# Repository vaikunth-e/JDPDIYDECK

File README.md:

STM32 audio effect processor with custom PCB

[Demo](https://youtu.be/CMMS7bL4tLE)

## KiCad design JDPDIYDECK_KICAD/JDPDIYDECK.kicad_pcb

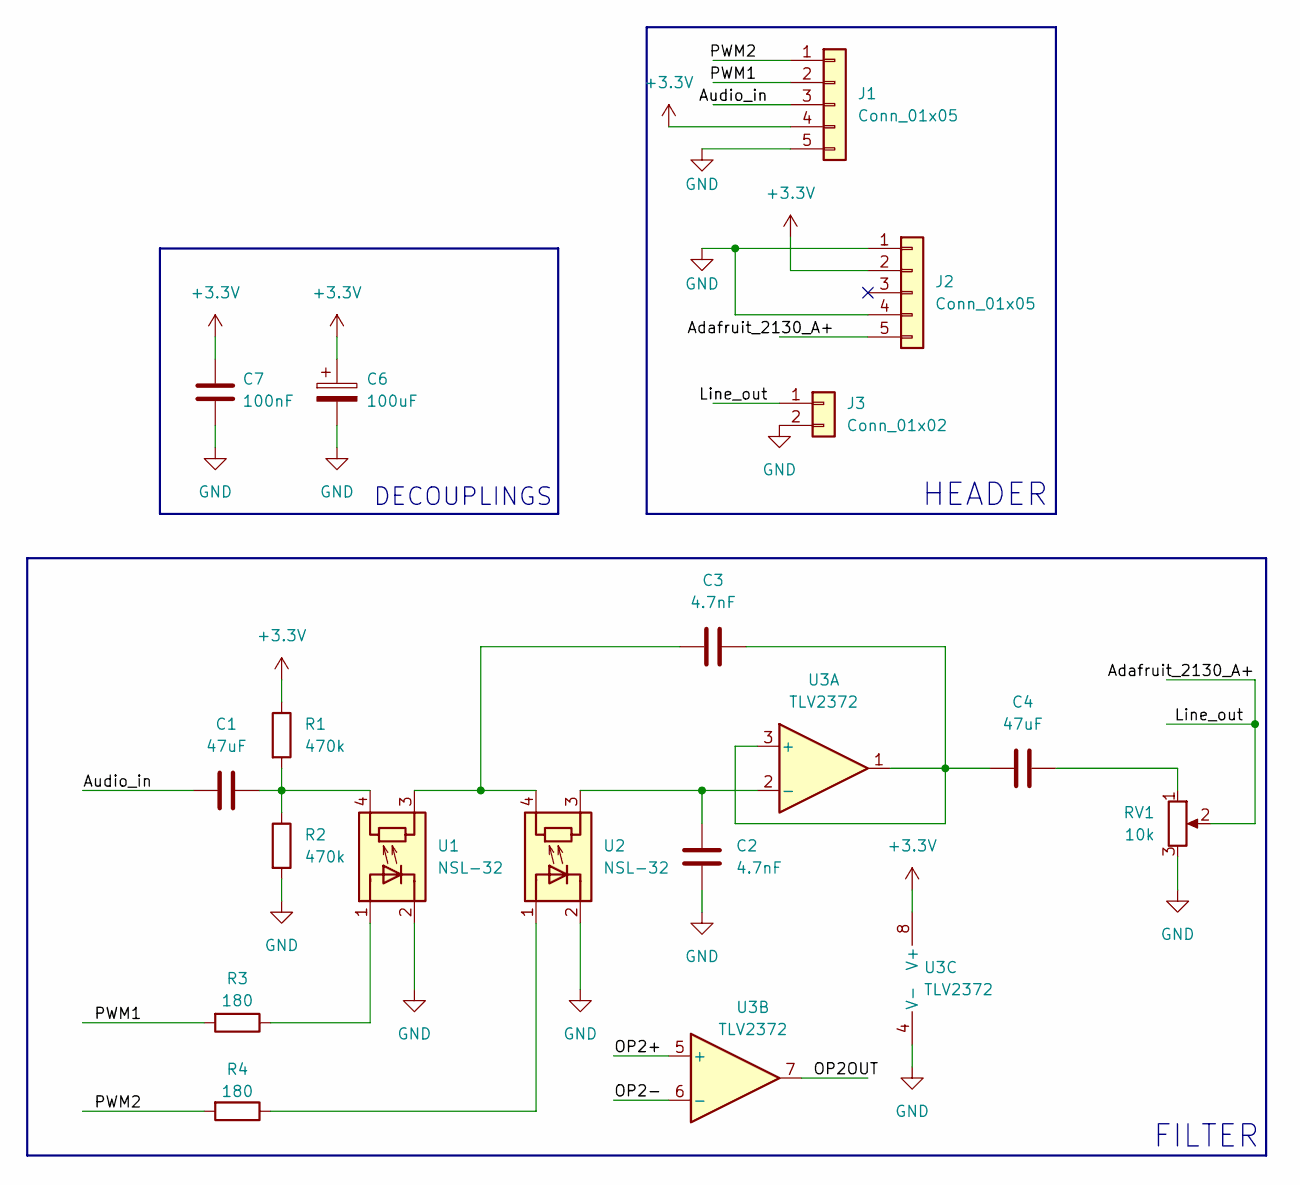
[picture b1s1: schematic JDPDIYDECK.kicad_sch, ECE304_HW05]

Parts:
C1, C4: 47uF; CAP_RDEC71E476MWK1H03B
C2, C3: 4.7nF; CAPRB500W50L400T250H550
C6: 100uF; CP_Radial_D5.0mm_P2.00mm
C7: 100nF; C_Rect_L4.0mm_W2.5mm_P2.50mm
J1: Conn_01x05; PinHeader_1x05_P2.54mm_Vertical
J2: Conn_01x05; PinSocket_1x05_P2.54mm_Vertical
J3: Conn_01x02; PinSocket_1x02_P2.54mm_Vertical
R1, R2: 470k; R_Axial_DIN0207_L6.3mm_D2.5mm_P10.16mm_Horizontal
R3, R4: 180; R_Axial_DIN0207_L6.3mm_D2.5mm_P10.16mm_Horizontal
RV1: 10k; Potentiometer_Bourns_PTV09A-1_Single_Vertical
U1, U2: NSL-32; Luna_NSL-32
U3: TLV2372; P8

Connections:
+3.3V: C6.1, C7.1, J1.4, J2.2, R1.1, U3.8 (V+)
/Adafruit_2130_A+: J2.5, J3.1, RV1.2
/Audio_in: C1.1, J1.3
/OP2+: U3.5 (+)
/OP2-: U3.6 (-)
/OP2OUT: U3.7
/PWM1: J1.2, R3.2
/PWM2: J1.1, R4.2
GND: C2.2, C6.2, C7.2, J1.5, J2.1, J2.4, J3.2, R2.2, RV1.3, U1.2 (K), U2.2 (K), U3.4 (V-)
unnamed: C1.2, R1.2, R2.1, U1.4 (R)
unnamed: C3.2, U1.3 (R), U2.4 (R)
unnamed: C4.2, RV1.1
unnamed: R3.1, U1.1 (A)
unnamed: R4.1, U2.1 (A)
unnamed: C3.1, C4.1, U3.1, U3.3 (+)
unnamed: C2.1, U2.3 (R), U3.2 (-)

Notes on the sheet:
HEADER
DECOUPLINGS
FILTER

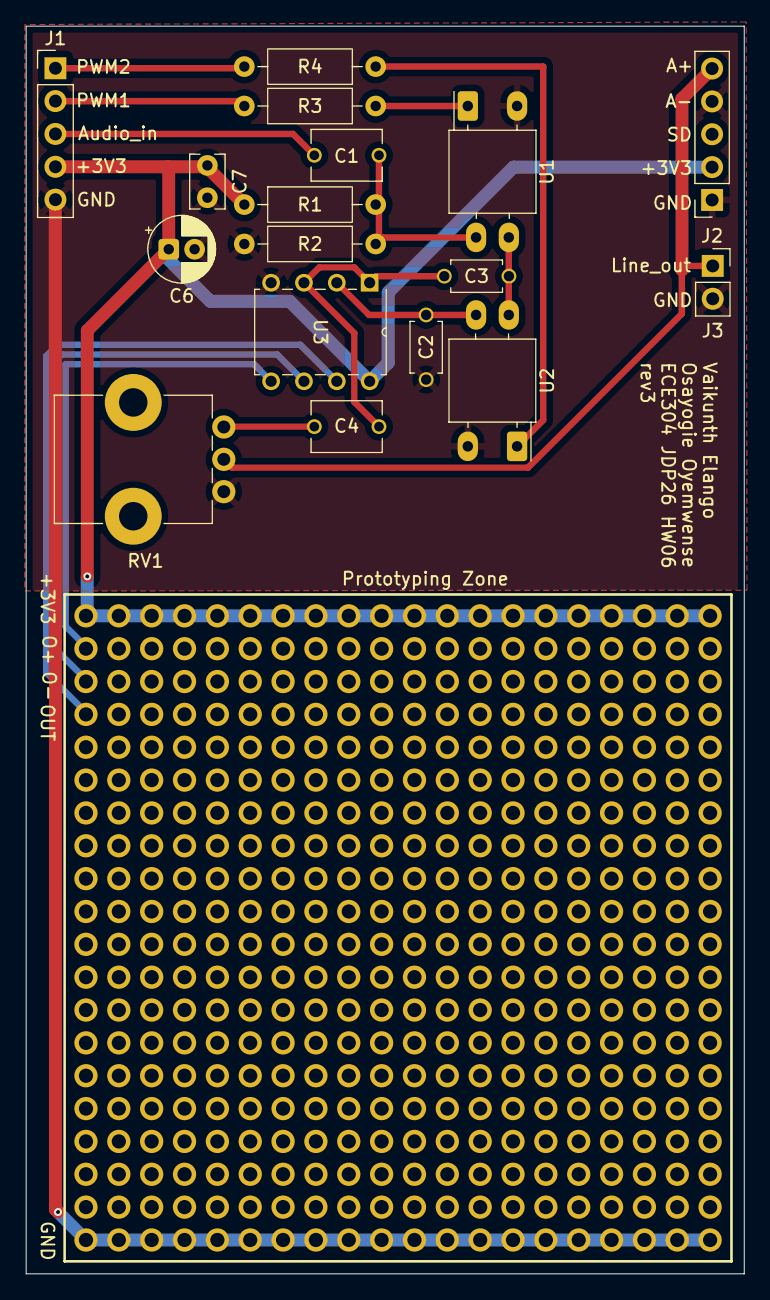
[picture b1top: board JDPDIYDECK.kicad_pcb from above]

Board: 2 copper layers, 55.5 x 96.5 mm, 17 parts (0 on the bottom side), 13 nets.

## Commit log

2026-04-25 circuit schematic
2026-04-26 KICAD files
2026-05-06 minor changes
2026-05-06 added button + 44.1 kHz
2026-05-08 ring modulation with triangle
2026-05-08 minor change
2026-05-12 Update project description in README
2026-05-12 Add demo link to README
2026-05-12 Fix formatting of README.md
